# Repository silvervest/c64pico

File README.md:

# C64 Pico

This is a tiny emulated C64 running on a Raspberry Pi Pico! Full details of the build can be found at https://www.youtube.com/watch?v=hgLhGpbC6E4

It was designed to dangle around my neck from a lanyard while I was wandering the halls and sections of PAX Aus 2022. It measures 102x81x16mm!

## Building

Wanna build one yourself? I go over the full build steps of this in the video linked above!

### BOM

I've put together an interactive BOM that you can reference - simply checkout the repo and open `ibom.html` in your browser.

Most of the parts can be figured out from the BOM or schematic, or are generic enough to just pick whatever fits (like all the caps and resistors), but some are pretty specific - here's a few purchasing links from the various sellers I used during this build;

* MicroSD card slot - https://www.aliexpress.com/item/32906952129.html
* TFT LCD - https://www.aliexpress.com/item/32837085500.html
* LCD FPC connector - https://www.digikey.com.au/en/products/detail/cvilux-usa/CF4240FH0R0-05-NH/15793119
* Crappy speaker - https://www.digikey.com.au/en/products/detail/cui-devices/CPT-9019S-SMT-TR/6012432
* Power switch - https://www.digikey.com.au/en/products/detail/c-k/JS102011SAQN/1640095
* Tac switches - https://www.digikey.com.au/en/products/detail/c-k/PTS-647-SN70-SMTR2-LFS/9649854
* LiPo battery - https://www.ebay.com.au/itm/143873020947

### PCBs

I designed the board to be fabricated specifically at JLCPCB with their SMT assembly service, so it should be pretty straightforward to get those made up.

Follow JLCPCB's guide on generating their bom and pos files from Kicad, and the components that can be placed by their SMT assembly service already have the correct and matching LCSC part number associated. Only the back layer needs assembly.

### Programming

The software provided for both the keyboard and MCUME modifications are not what I'd call "production-ready" either, and are really just a hack job. I might clean them up to be merged back one day, but probably not.

The keyboard code is in this repo underneath the keyboard directory, and can be programmed directly onto the ATmega328PB via ICSP headers using the Arduino software.

The RPi Pico code can be found in [my fork of the MCUME repo](https://github.com/silvervest/MCUME/tree/c64pico) under branch `c64pico` and you can follow the main instructions for building, installation and use.

### Face and back plates

The faceplate is just a plain PCB, and the PCB design files can be provided to your fab like any other. I recommend getting it HASL gold covered for extra shiny.

The backplate was designed to be laser cut from 1.5mm-2mm acrylic. I had mine created by [The Laser Cut Shop](https://thelasercutshop.com.au/) and the team there were excellent. I used the plotting function in KiCad to export DXF files for them to use.

## Instructions

Once it's complete, pop your SD card with .PRG files available into the slot and switch it on.

Pick whatever program you'd like to open and press the FIRE joystick button "pew pew". By default, the built-in joystick is "plugged" into JOY1 port, and you can switch that between JOY1/JOY2 using F1/F3 keys. Most C64 games use JOY2, so you might need to experiment.

At the BASIC prompt, type `LOAD` and press RETURN. That will load the .PRG file contents into RAM. Once READY, type `RUN` and press RETURN.

Enjoy! It's a bit slow, and some games are buggy as hell. I love playing Nebulus and Choplifter :)

## Development Photos

An early design, showing the overengineered reimplementation of the RP2040 Pico circuit and power management. It worked, but I didn't like it, so threw most of it out. You can also see I added full diodes into the keyboard for the hell of it.

This was when I was writing the Arduino code for the keyboard and I2C protocol, and a test program running on the Pico decoding it and showing the output.

Finally fully working, so I booted up my favourite C64 game - Nebulus! The screen and battery were still held on with washi tape here.

Also Burnin' Rubber because that game is awesome and runs at almost full speed with no bugs that I could find!

And of course, I've gotta run the classic [10print maze](https://10print.org/)

## Acknowledgements

 - [MCUME](https://github.com/Jean-MarcHarvengt/MCUME)

    The base emulator at the guts of this, and was modified for my purposes.

 - [PICOmputer](https://github.com/bobricius/PICOmputer)

    Heavy inspiration taken from this project (and I stole the UDLR joystick layout)

## License

[CERN OHL v2 Strongly Reciprocal](https://choosealicense.com/licenses/cern-ohl-s-2.0/)

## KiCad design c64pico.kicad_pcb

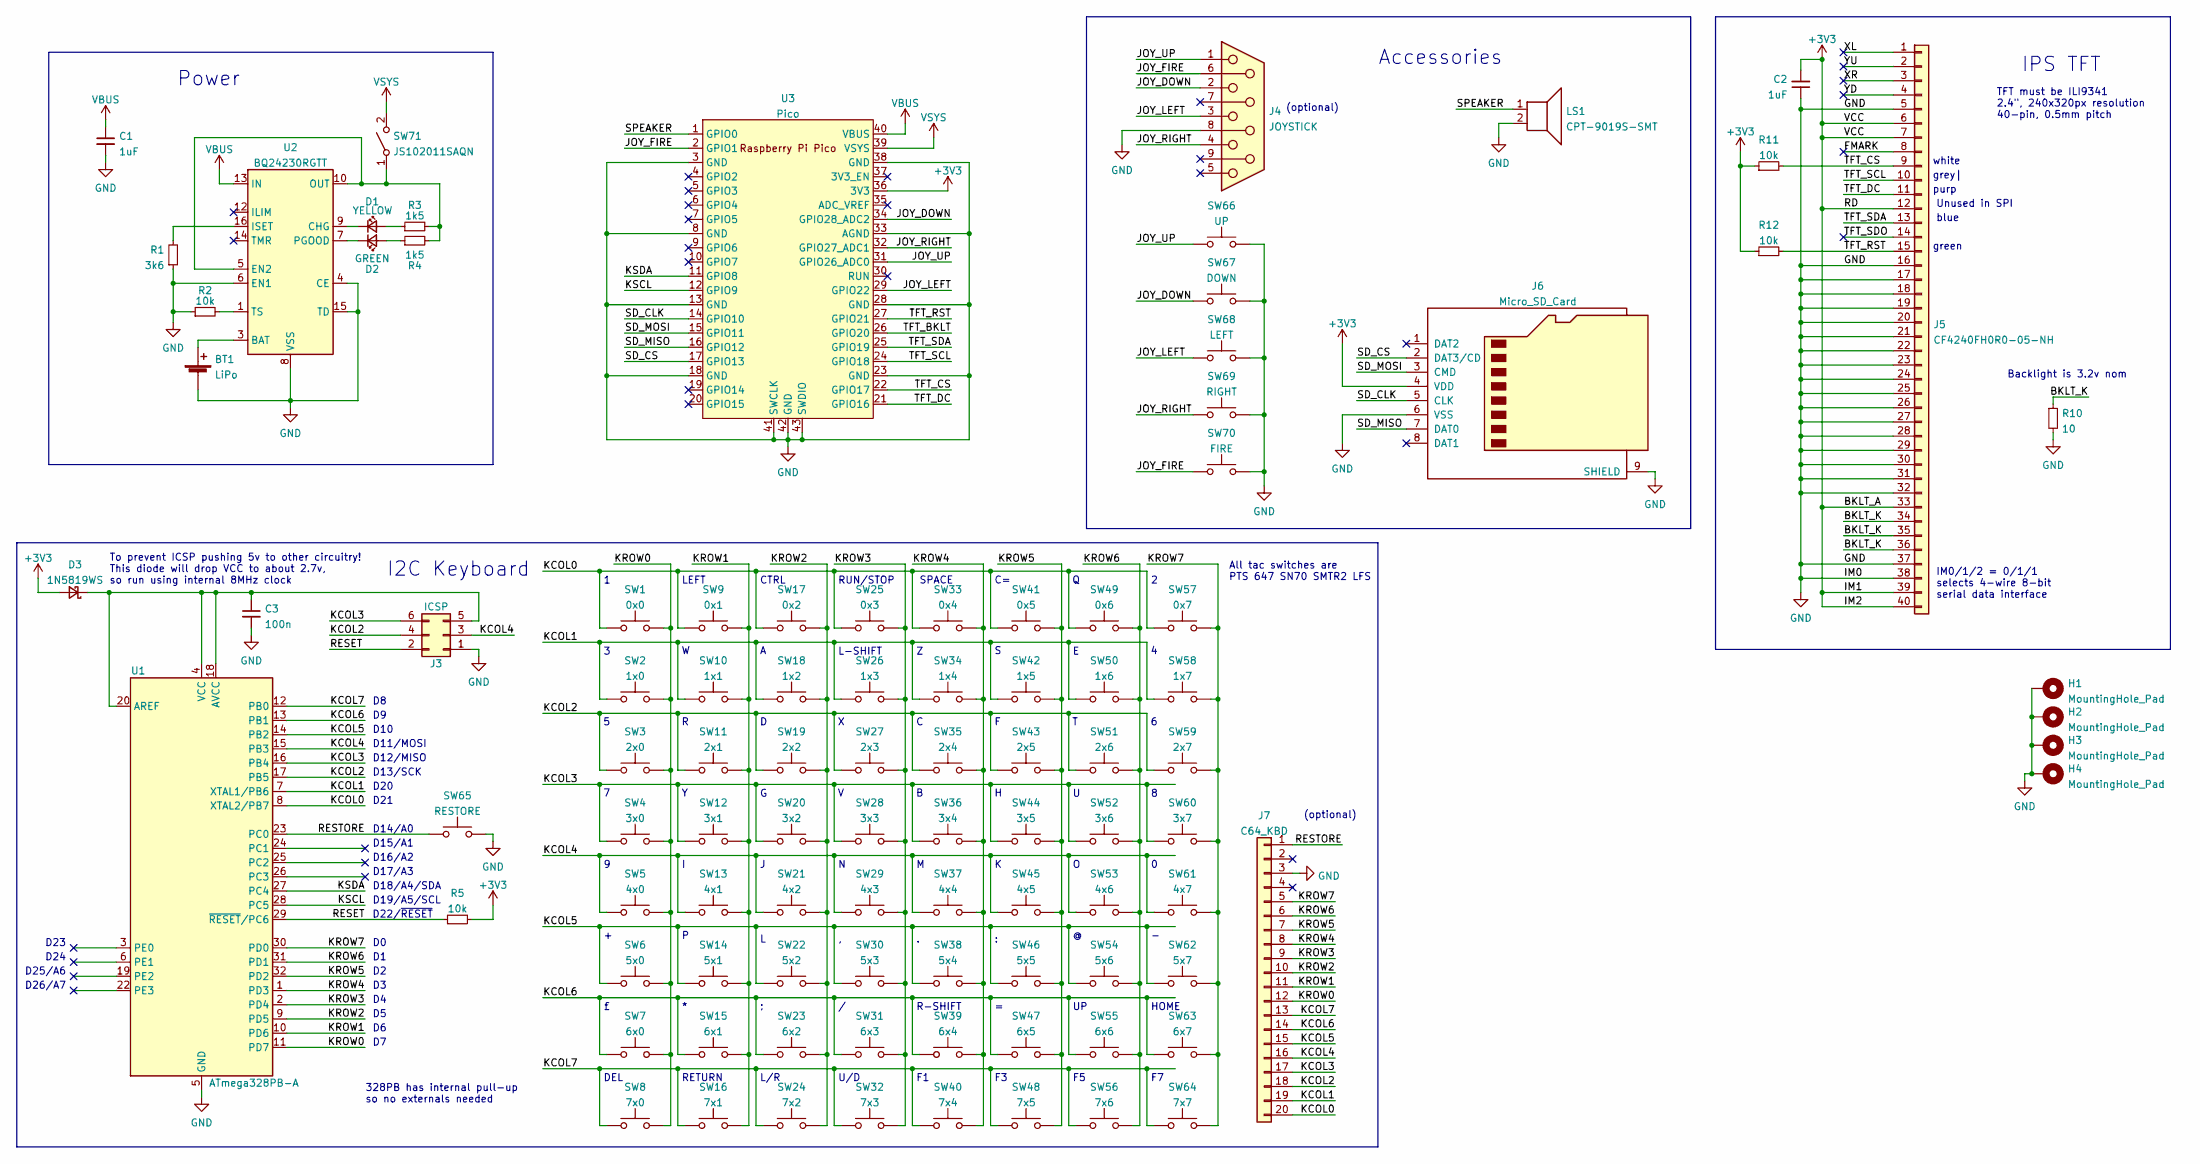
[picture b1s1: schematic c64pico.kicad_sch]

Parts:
BT1: LiPo; JST_PH_S2B-PH-K_1x02_P2.00mm_Horizontal
C1, C2: 1uF; C_0402_1005Metric; LCSC C52923
C3: 100n; C_0402_1005Metric; LCSC C1525
D1: YELLOW; LED_0603_1608Metric; LCSC C72038
D2: GREEN; LED_0603_1608Metric; LCSC C72043
D3: 1N5819WS; D_SOD-323
H1, H2, H3, H4: MountingHole_Pad; MountingHole_2.2mm_M2_Pad
J3: ICSP; PinHeader_2x03_P2.54mm_Vertical
J4: JOYSTICK
J5: CF4240FH0R0-05-NH; ILI9341
J6: Micro_SD_Card; Conn_uSDcard
J7: C64_KBD; PinHeader_1x20_P2.54mm_Vertical
LS1: CPT-9019S-SMT; Buzzer_CUI_CPT-9019S-SMT
R1: 3k6; R_0603_1608Metric; LCSC C22980
R2, R5, R11, R12: 10k; R_0402_1005Metric; LCSC C25744
R3, R4: 1k5; R_0402_1005Metric; LCSC C25867
R10: 10; R_0402_1005Metric
SW1: 0x0; SW_SPST_PTS647
SW2: 1x0; SW_SPST_PTS647
SW3: 2x0; SW_SPST_PTS647
SW4: 3x0; SW_SPST_PTS647
SW5: 4x0; SW_SPST_PTS647
SW6: 5x0; SW_SPST_PTS647
SW7: 6x0; SW_SPST_PTS647
SW8: 7x0; SW_SPST_PTS647
SW9: 0x1; SW_SPST_PTS647
SW10: 1x1; SW_SPST_PTS647
SW11: 2x1; SW_SPST_PTS647
SW12: 3x1; SW_SPST_PTS647
SW13: 4x1; SW_SPST_PTS647
SW14: 5x1; SW_SPST_PTS647
SW15: 6x1; SW_SPST_PTS647
SW16: 7x1; SW_SPST_PTS647
SW17: 0x2; SW_SPST_PTS647
SW18: 1x2; SW_SPST_PTS647
SW19: 2x2; SW_SPST_PTS647
SW20: 3x2; SW_SPST_PTS647
SW21: 4x2; SW_SPST_PTS647
SW22: 5x2; SW_SPST_PTS647
SW23: 6x2; SW_SPST_PTS647
SW24: 7x2; SW_SPST_PTS647
SW25: 0x3; SW_SPST_PTS647
SW26: 1x3; SW_SPST_PTS647
SW27: 2x3; SW_SPST_PTS647
SW28: 3x3; SW_SPST_PTS647
SW29: 4x3; SW_SPST_PTS647
SW30: 5x3; SW_SPST_PTS647
SW31: 6x3; SW_SPST_PTS647
SW32: 7x3; SW_SPST_PTS647
SW33: 0x4; SW_SPST_PTS647
SW34: 1x4; SW_SPST_PTS647
SW35: 2x4; SW_SPST_PTS647
SW36: 3x4; SW_SPST_PTS647
SW37: 4x4; SW_SPST_PTS647
SW38: 5x4; SW_SPST_PTS647
SW39: 6x4; SW_SPST_PTS647
SW40: 7x4; SW_SPST_PTS647
SW41: 0x5; SW_SPST_PTS647
SW42: 1x5; SW_SPST_PTS647
SW43: 2x5; SW_SPST_PTS647
SW44: 3x5; SW_SPST_PTS647
SW45: 4x5; SW_SPST_PTS647
SW46: 5x5; SW_SPST_PTS647
SW47: 6x5; SW_SPST_PTS647
SW48: 7x5; SW_SPST_PTS647
SW49: 0x6; SW_SPST_PTS647
SW50: 1x6; SW_SPST_PTS647
SW51: 2x6; SW_SPST_PTS647
SW52: 3x6; SW_SPST_PTS647
SW53: 4x6; SW_SPST_PTS647
SW54: 5x6; SW_SPST_PTS647
SW55: 6x6; SW_SPST_PTS647
SW56: 7x6; SW_SPST_PTS647
SW57: 0x7; SW_SPST_PTS647
SW58: 1x7; SW_SPST_PTS647
SW59: 2x7; SW_SPST_PTS647
SW60: 3x7; SW_SPST_PTS647
SW61: 4x7; SW_SPST_PTS647
SW62: 5x7; SW_SPST_PTS647
SW63: 6x7; SW_SPST_PTS647
SW64: 7x7; SW_SPST_PTS647
SW65: RESTORE; SW_SPST_PTS647
SW66: UP; SW_SPST_PTS647
SW67: DOWN; SW_SPST_PTS647
SW68: LEFT; SW_SPST_PTS647
SW69: RIGHT; SW_SPST_PTS647
SW70: FIRE; SW_SPST_PTS647
SW71: JS102011SAQN; SW_SPDT_CK-JS102011SAQN
U1: ATmega328PB-A; TQFP-32_7x7mm_P0.8mm
U2: BQ24230RGTT; VQFN-16-1EP_3x3mm_P0.5mm_EP1.68x1.68mm_ThermalVias; LCSC C138361
U3: Pico; RPi_Pico_SMD

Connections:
+3V3: C2.2, D3.2 (A), J5.6, J5.7, J5.12, J5.33, J5.39, J5.40, J6.4 (VDD), R5.2, R11.1, R12.1, U3.36 (3V3)
/BKLT_K: J5.34, J5.35, J5.36, R10.1
/FMARK: J5.8
/JOY_DOWN: J4.2, SW67.1, U3.34 (GPIO28_ADC2)
/JOY_FIRE: J4.6, SW70.1, U3.2 (GPIO1)
/JOY_LEFT: J4.3, SW68.1, U3.29 (GPIO22)
/JOY_RIGHT: J4.4, SW69.1, U3.32 (GPIO27_ADC1)
/JOY_UP: J4.1, SW66.1, U3.31 (GPIO26_ADC0)
/KCOL0: J7.20, SW1.1, SW9.1, SW17.1, SW25.1, SW33.1, SW41.1, SW49.1, SW57.1, U1.8 (XTAL2/PB7)
/KCOL1: J7.19, SW2.1, SW10.1, SW18.1, SW26.1, SW34.1, SW42.1, SW50.1, SW58.1, U1.7 (XTAL1/PB6)
/KCOL2: J3.4, J7.18, SW3.1, SW11.1, SW19.1, SW27.1, SW35.1, SW43.1, SW51.1, SW59.1, U1.17 (PB5)
/KCOL3: J3.6, J7.17, SW4.1, SW12.1, SW20.1, SW28.1, SW36.1, SW44.1, SW52.1, SW60.1, U1.16 (PB4)
/KCOL4: J3.3, J7.16, SW5.1, SW13.1, SW21.1, SW29.1, SW37.1, SW45.1, SW53.1, SW61.1, U1.15 (PB3)
/KCOL5: J7.15, SW6.1, SW14.1, SW22.1, SW30.1, SW38.1, SW46.1, SW54.1, SW62.1, U1.14 (PB2)
/KCOL6: J7.14, SW7.1, SW15.1, SW23.1, SW31.1, SW39.1, SW47.1, SW55.1, SW63.1, U1.13 (PB1)
/KCOL7: J7.13, SW8.1, SW16.1, SW24.1, SW32.1, SW40.1, SW48.1, SW56.1, SW64.1, U1.12 (PB0)
/KROW0: J7.12, SW1.2, SW2.2, SW3.2, SW4.2, SW5.2, SW6.2, SW7.2, SW8.2, U1.11 (PD7)
/KROW1: J7.11, SW9.2, SW10.2, SW11.2, SW12.2, SW13.2, SW14.2, SW15.2, SW16.2, U1.10 (PD6)
/KROW2: J7.10, SW17.2, SW18.2, SW19.2, SW20.2, SW21.2, SW22.2, SW23.2, SW24.2, U1.9 (PD5)
/KROW3: J7.9, SW25.2, SW26.2, SW27.2, SW28.2, SW29.2, SW30.2, SW31.2, SW32.2, U1.2 (PD4)
/KROW4: J7.8, SW33.2, SW34.2, SW35.2, SW36.2, SW37.2, SW38.2, SW39.2, SW40.2, U1.1 (PD3)
/KROW5: J7.7, SW41.2, SW42.2, SW43.2, SW44.2, SW45.2, SW46.2, SW47.2, SW48.2, U1.32 (PD2)
/KROW6: J7.6, SW49.2, SW50.2, SW51.2, SW52.2, SW53.2, SW54.2, SW55.2, SW56.2, U1.31 (PD1)
/KROW7: J7.5, SW57.2, SW58.2, SW59.2, SW60.2, SW61.2, SW62.2, SW63.2, SW64.2, U1.30 (PD0)
/KSCL: U1.28 (PC5), U3.12 (GPIO9)
/KSDA: U1.27 (PC4), U3.11 (GPIO8)
/RESET: J3.2, R5.1, U1.29 (~RESET/PC6)
/RESTORE: J7.1, SW65.1, U1.23 (PC0)
/SD_CLK: J6.5 (CLK), U3.14 (GPIO10)
/SD_CS: J6.2 (DAT3/CD), U3.17 (GPIO13)
/SD_MISO: J6.7 (DAT0), U3.16 (GPIO12)
/SD_MOSI: J6.3 (CMD), U3.15 (GPIO11)
/SPEAKER: LS1.1, U3.1 (GPIO0)
/TFT_BKLT: U3.26 (GPIO20)
/TFT_CS: J5.9, R11.2, U3.22 (GPIO17)
/TFT_DC: J5.11, U3.21 (GPIO16)
/TFT_RST: J5.15, R12.2, U3.27 (GPIO21)
/TFT_SCL: J5.10, U3.24 (GPIO18)
/TFT_SDA: J5.13, U3.25 (GPIO19)
/TFT_SDO: J5.14
/XL: J5.1
/XR: J5.3
/YD: J5.4
/YU: J5.2
GND: BT1.2 (-), C1.2, C2.1, C3.2, H1.1, H2.1, H3.1, H4.1, J3.1, J4.8, J5.5, J5.16, J5.17, J5.18, J5.19, J5.20, J5.21, J5.22, J5.23, J5.24, J5.25, J5.26, J5.27, J5.28, J5.29, J5.30, J5.31, J5.32, J5.37, J5.38, J6.6 (VSS), J6.9 (SHIELD), J7.3, LS1.2, R1.1, R2.1, R10.2, SW65.2, SW66.2, SW67.2, SW68.2, SW69.2, SW70.2, U1.5 (GND), U1.21 (GND), U2.4 (CE), U2.6 (EN1), U2.8 (VSS), U2.15 (TD), U2.17 (VSS), U3.3 (GND), U3.8 (GND), U3.13 (GND), U3.18 (GND), U3.23 (GND), U3.28 (GND), U3.33 (AGND), U3.38 (GND), U3.41 (SWCLK), U3.42 (GND), U3.43 (SWDIO)
unnamed: BT1.1 (+), U2.2 (BAT), U2.3 (BAT)
unnamed: C3.1, D3.1 (K), J3.5, U1.4 (VCC), U1.18 (AVCC), U1.20 (AREF)
unnamed: D1.1 (K), U2.9 (CHG)
unnamed: D1.2 (A), R3.1
unnamed: D2.1 (K), U2.7 (PGOOD)
unnamed: D2.2 (A), R4.1
unnamed: R1.2, U2.16 (ISET)
unnamed: R2.2, U2.1 (TS)
unnamed: R3.2, R4.2, SW71.1 (A), U2.5 (EN2), U2.10 (OUT), U2.11 (OUT)
VBUS: C1.1, U2.13 (IN), U3.40 (VBUS)
VSYS: SW71.2 (B), U3.39 (VSYS)

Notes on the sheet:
D22/~{RESET}
LEFT
All tac switches are PTS 647 SN70 SMTR2 LFS
D20
328PB has internal pull-up so no externals needed
TFT must be ILI9341 2.4", 240x320px resolution 40-pin, 0.5mm pitch
To prevent ICSP pushing 5v to other circuitry! This diode will drop VCC to about 2.7v, so run using internal 8MHz clock
RUN/STOP
RETURN
U/D
purp
D19/A5/SCL
R-SHIFT
Accessories
D21
Backlight is 3.2v nom
D11/MOSI
SPACE
CTRL
IM0/1/2 = 0/1/1 selects 4-wire 8-bit serial data interface
L/R
grey|
D25/A6
(optional)
D14/A0
white
HOME
I2C Keyboard
D23
Power
blue
D10
D13/SCK
D12/MISO
D18/A4/SDA
L-SHIFT
D26/A7
DEL
IPS TFT
D24

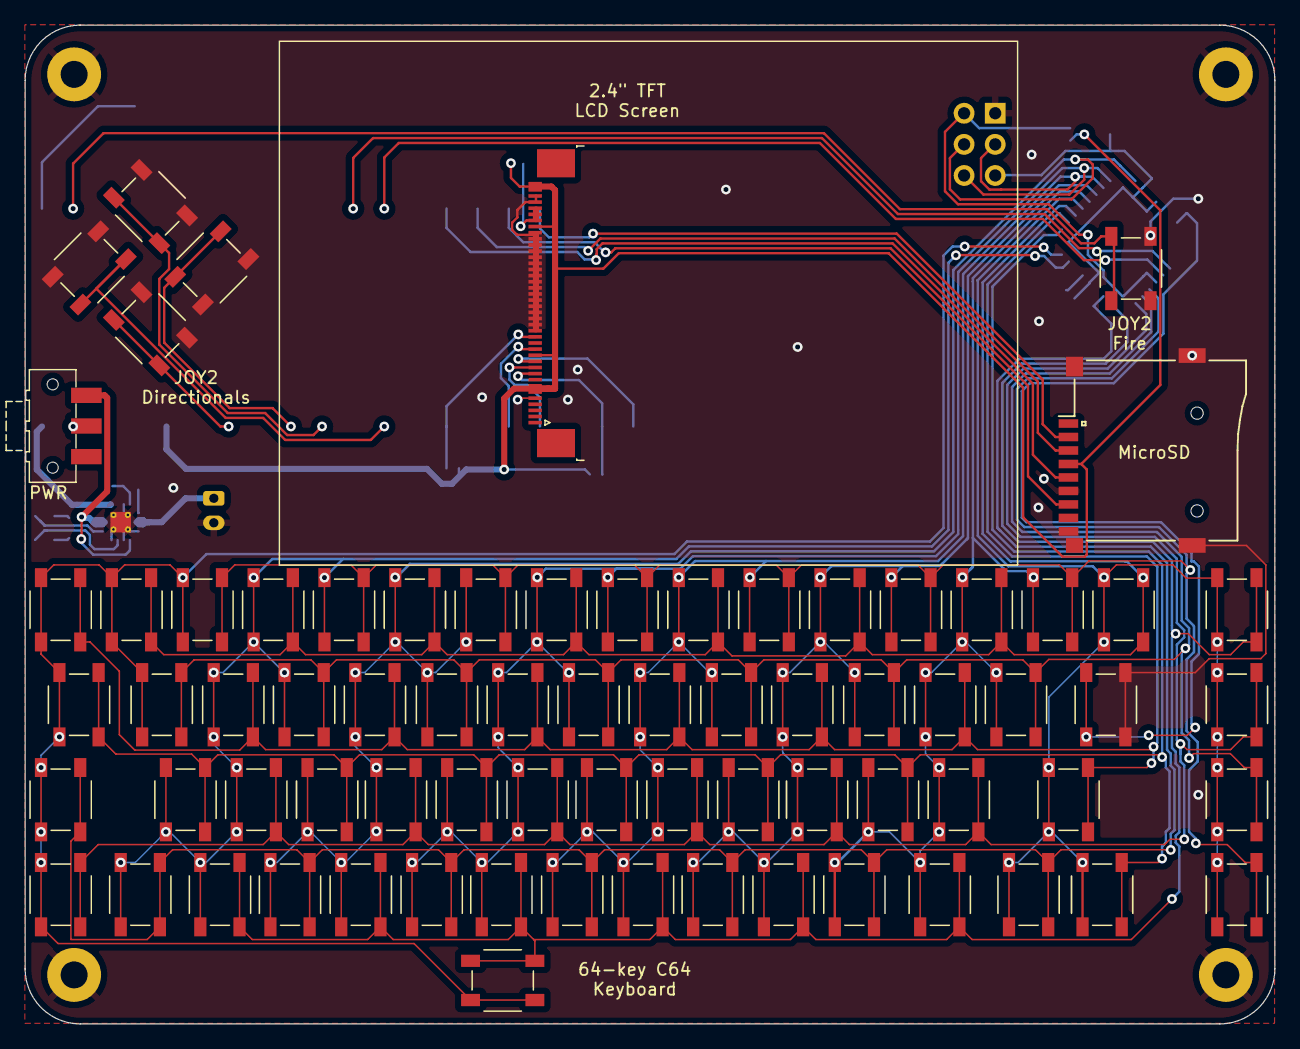
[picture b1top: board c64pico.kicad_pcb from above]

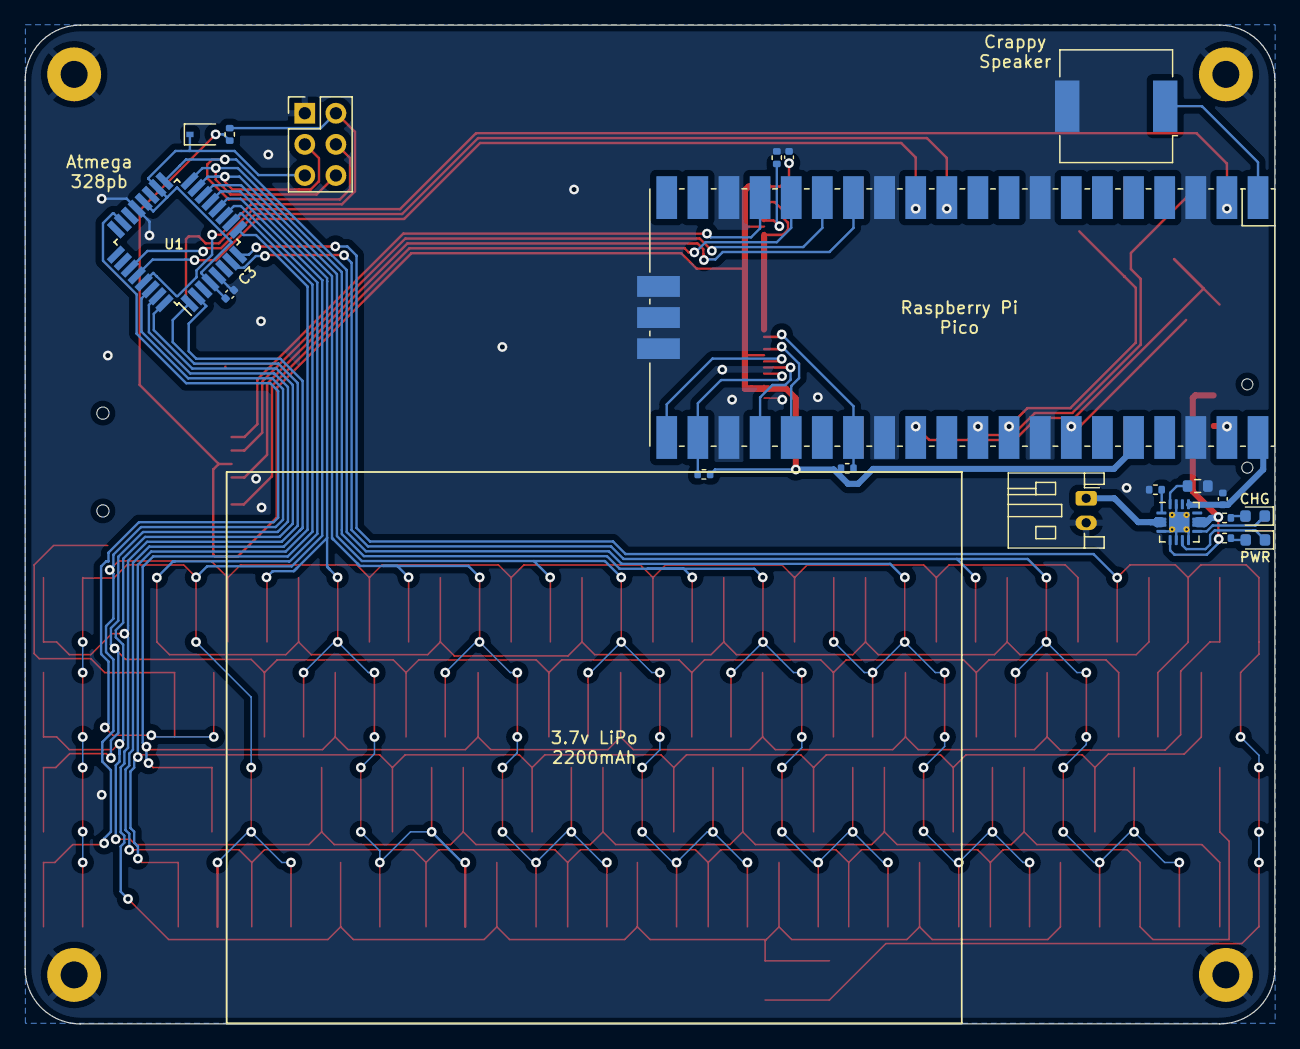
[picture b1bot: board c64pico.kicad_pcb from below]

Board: 2 copper layers, 102.0 x 81.5 mm, 97 parts (20 on the bottom side), 49 nets.

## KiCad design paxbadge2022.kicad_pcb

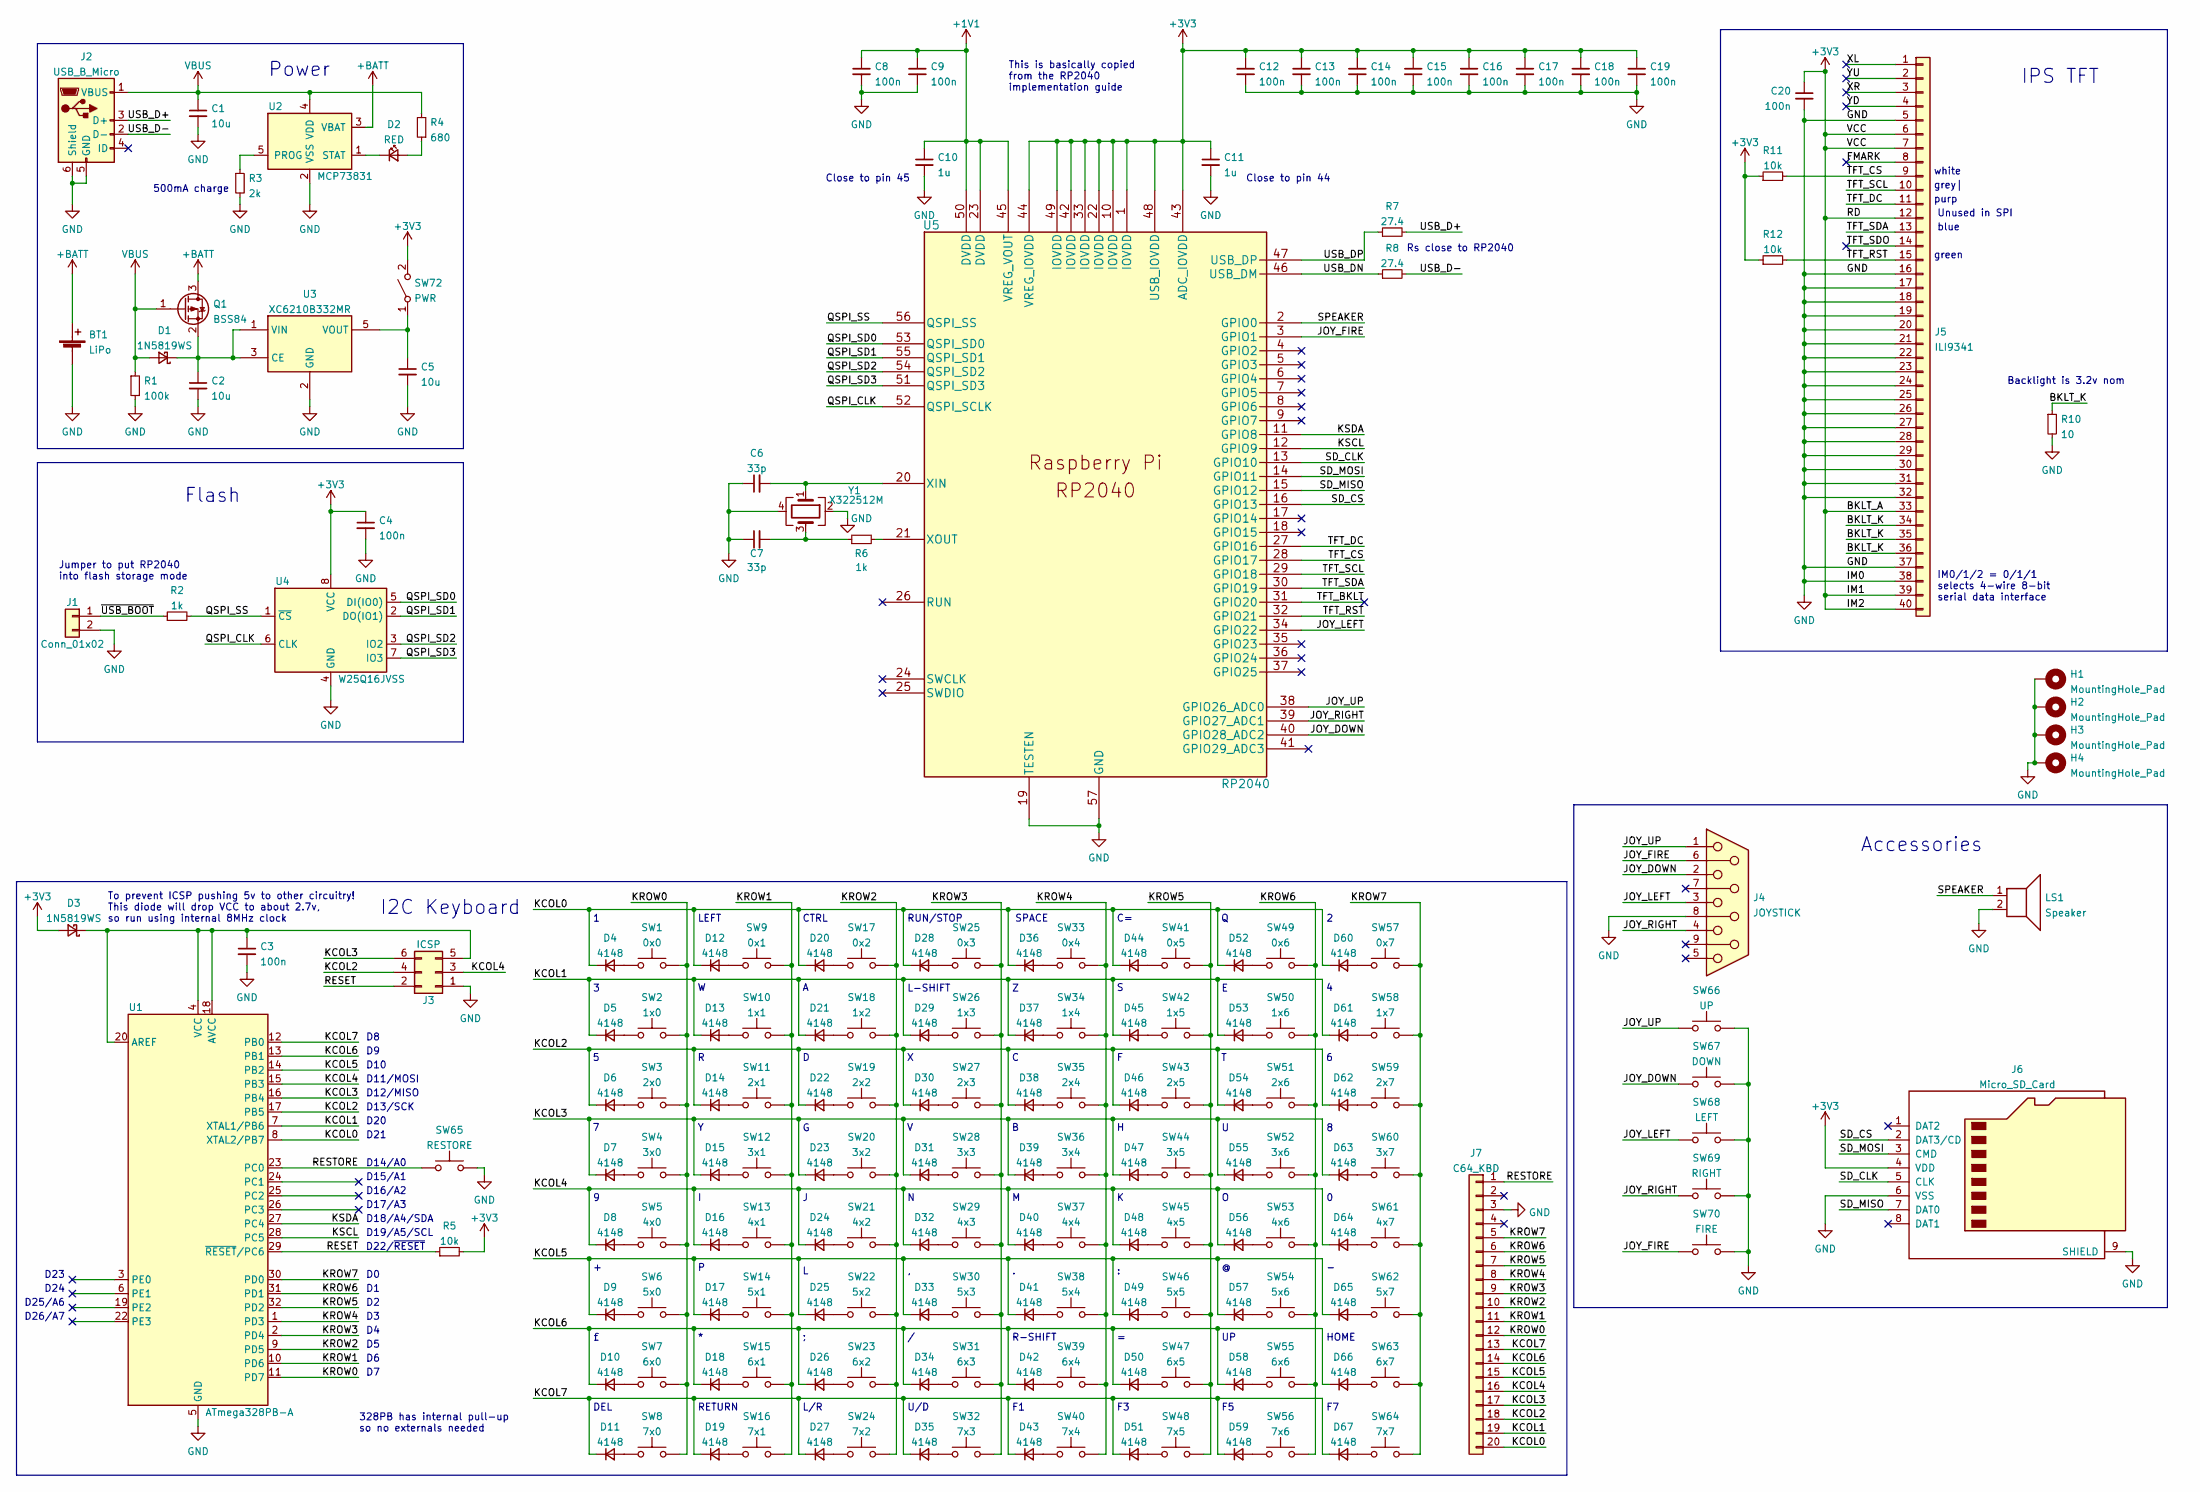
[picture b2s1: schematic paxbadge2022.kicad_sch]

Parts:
BT1: LiPo; JST_PH_S2B-PH-K_1x02_P2.00mm_Horizontal
C1, C2, C5: 10u; C_0603_1608Metric; LCSC C19702
C3, C4: 100n; C_0402_1005Metric; LCSC C1525
C6: 33p; C_0402_1005Metric; LCSC C1562
C7: 33p; C_0402_1005Metric
C8, C9, C12, C13, C14, C15, C16, C17, C18, C19, C20: 100n; C_0402_1005Metric
C10: 1u; C_0402_1005Metric; LCSC C52923
C11: 1u; C_0402_1005Metric
D1: 1N5819WS; D_SOD-323; LCSC C191023
D2: RED; LED_D3.0mm; LCSC C2286
D3: 1N5819WS; D_SOD-323
D4, D5, D6, D7, D8, D9, D10, D11, D12, D13, D14, D15, D16, D17, D18, D19, D20, D21, D22, D23, D24, D25, D26, D27, D28, D29, D30, D31, D32, D33, D34, D35, D36, D37, D38, D39, D40, D41, D42, D43, D44, D45, D46, D47, D48, D49, D50, D51, D52, D53, D54, D55, D56, D57, D58, D59, D60, D61, D62, D63, D64, D65, D66, D67: 4148; D_SOD-323F
H1, H2, H3, H4: MountingHole_Pad; MountingHole_2.2mm_M2_Pad
J1: Conn_01x02; PinHeader_1x02_P2.54mm_Vertical
J2: USB_B_Micro; USB_Micro-B_Amphenol_10118194_Horizontal
J3: ICSP; PinHeader_2x03_P2.54mm_Vertical
J4: JOYSTICK
J5: ILI9341
J6: Micro_SD_Card; Conn_uSDcard
J7: C64_KBD; PinHeader_1x20_P2.54mm_Vertical
LS1: Speaker; Buzzer_CUI_CPT-9019S-SMT
Q1: BSS84; SOT-23; LCSC C8492
R1: 100k; R_0402_1005Metric; LCSC C25741
R2: 1k; R_0402_1005Metric; LCSC C11702
R3: 2k; R_0402_1005Metric; LCSC C4109
R4: 680; R_0402_1005Metric; LCSC C25130
R5, R11, R12: 10k; R_0402_1005Metric; LCSC C25744
R6: 1k; R_0402_1005Metric
R7: 27.4; R_0402_1005Metric; LCSC C25100
R8: 27.4; R_0402_1005Metric
R10: 10; R_0402_1005Metric
SW1: 0x0; SW_SPST_PTS647
SW2: 1x0; SW_SPST_PTS647
SW3: 2x0; SW_SPST_PTS647
SW4: 3x0; SW_SPST_PTS647
SW5: 4x0; SW_SPST_PTS647
SW6: 5x0; SW_SPST_PTS647
SW7: 6x0; SW_SPST_PTS647
SW8: 7x0; SW_SPST_PTS647
SW9: 0x1; SW_SPST_PTS647
SW10: 1x1; SW_SPST_PTS647
SW11: 2x1; SW_SPST_PTS647
SW12: 3x1; SW_SPST_PTS647
SW13: 4x1; SW_SPST_PTS647
SW14: 5x1; SW_SPST_PTS647
SW15: 6x1; SW_SPST_PTS647
SW16: 7x1; SW_SPST_PTS647
SW17: 0x2; SW_SPST_PTS647
SW18: 1x2; SW_SPST_PTS647
SW19: 2x2; SW_SPST_PTS647
SW20: 3x2; SW_SPST_PTS647
SW21: 4x2; SW_SPST_PTS647
SW22: 5x2; SW_SPST_PTS647
SW23: 6x2; SW_SPST_PTS647
SW24: 7x2; SW_SPST_PTS647
SW25: 0x3; SW_SPST_PTS647
SW26: 1x3; SW_SPST_PTS647
SW27: 2x3; SW_SPST_PTS647
SW28: 3x3; SW_SPST_PTS647
SW29: 4x3; SW_SPST_PTS647
SW30: 5x3; SW_SPST_PTS647
SW31: 6x3; SW_SPST_PTS647
SW32: 7x3; SW_SPST_PTS647
SW33: 0x4; SW_SPST_PTS647
SW34: 1x4; SW_SPST_PTS647
SW35: 2x4; SW_SPST_PTS647
SW36: 3x4; SW_SPST_PTS647
SW37: 4x4; SW_SPST_PTS647
SW38: 5x4; SW_SPST_PTS647
SW39: 6x4; SW_SPST_PTS647
SW40: 7x4; SW_SPST_PTS647
SW41: 0x5; SW_SPST_PTS647
SW42: 1x5; SW_SPST_PTS647
SW43: 2x5; SW_SPST_PTS647
SW44: 3x5; SW_SPST_PTS647
SW45: 4x5; SW_SPST_PTS647
SW46: 5x5; SW_SPST_PTS647
SW47: 6x5; SW_SPST_PTS647
SW48: 7x5; SW_SPST_PTS647
SW49: 0x6; SW_SPST_PTS647
SW50: 1x6; SW_SPST_PTS647
SW51: 2x6; SW_SPST_PTS647
SW52: 3x6; SW_SPST_PTS647
SW53: 4x6; SW_SPST_PTS647
SW54: 5x6; SW_SPST_PTS647
SW55: 6x6; SW_SPST_PTS647
SW56: 7x6; SW_SPST_PTS647
SW57: 0x7; SW_SPST_PTS647
SW58: 1x7; SW_SPST_PTS647
SW59: 2x7; SW_SPST_PTS647
SW60: 3x7; SW_SPST_PTS647
SW61: 4x7; SW_SPST_PTS647
SW62: 5x7; SW_SPST_PTS647
SW63: 6x7; SW_SPST_PTS647
SW64: 7x7; SW_SPST_PTS647
SW65: RESTORE; SW_SPST_PTS647
SW66: UP; SW_SPST_PTS647
SW67: DOWN; SW_SPST_PTS647
SW68: LEFT; SW_SPST_PTS647
SW69: RIGHT; SW_SPST_PTS647
SW70: FIRE; SW_SPST_PTS647
SW72: PWR; SW_SPDT_CK-JS102011SAQN
U1: ATmega328PB-A; TQFP-32_7x7mm_P0.8mm
U2: MCP73831; SOT-23-5; LCSC C14879
U3: XC6210B332MR; SOT-23-5; LCSC C47719
U4: W25Q16JVSS; SOIC-8_5.23x5.23mm_P1.27mm; LCSC C82317
U5: RP2040; LCSC C2040
Y1: X322512M; Crystal_SMD_3225-4Pin_3.2x2.5mm; LCSC C9002

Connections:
+1V1: C8.1, C9.1, C10.1, U5.23 (DVDD), U5.45 (VREG_VOUT), U5.50 (DVDD)
+3V3: C4.1, C11.1, C12.1, C13.1, C14.1, C15.1, C16.1, C17.1, C18.1, C19.1, C20.1, D3.2 (A), J5.6, J5.7, J5.12, J5.33, J5.39, J5.40, J6.4 (VDD), R5.2, R11.1, R12.1, SW72.2 (B), U4.8 (VCC), U5.1 (IOVDD), U5.10 (IOVDD), U5.22 (IOVDD), U5.33 (IOVDD), U5.42 (IOVDD), U5.43 (ADC_IOVDD), U5.44 (VREG_IOVDD), U5.48 (USB_IOVDD), U5.49 (IOVDD)
+BATT: BT1.1 (+), Q1.3 (D), U2.3 (VBAT)
/BKLT_K: J5.34, J5.35, J5.36, R10.1
/FMARK: J5.8
/JOY_DOWN: J4.2, SW67.1, U5.40 (GPIO28_ADC2)
/JOY_FIRE: J4.6, SW70.1, U5.3 (GPIO1)
/JOY_LEFT: J4.3, SW68.1, U5.34 (GPIO22)
/JOY_RIGHT: J4.4, SW69.1, U5.39 (GPIO27_ADC1)
/JOY_UP: J4.1, SW66.1, U5.38 (GPIO26_ADC0)
/KCOL0: D4.1 (K), D12.1 (K), D20.1 (K), D28.1 (K), D36.1 (K), D44.1 (K), D52.1 (K), D60.1 (K), J7.20, U1.8 (XTAL2/PB7)
/KCOL1: D5.1 (K), D13.1 (K), D21.1 (K), D29.1 (K), D37.1 (K), D45.1 (K), D53.1 (K), D61.1 (K), J7.19, U1.7 (XTAL1/PB6)
/KCOL2: D6.1 (K), D14.1 (K), D22.1 (K), D30.1 (K), D38.1 (K), D46.1 (K), D54.1 (K), D62.1 (K), J3.4, J7.18, U1.17 (PB5)
/KCOL3: D7.1 (K), D15.1 (K), D23.1 (K), D31.1 (K), D39.1 (K), D47.1 (K), D55.1 (K), D63.1 (K), J3.6, J7.17, U1.16 (PB4)
/KCOL4: D8.1 (K), D16.1 (K), D24.1 (K), D32.1 (K), D40.1 (K), D48.1 (K), D56.1 (K), D64.1 (K), J3.3, J7.16, U1.15 (PB3)
/KCOL5: D9.1 (K), D17.1 (K), D25.1 (K), D33.1 (K), D41.1 (K), D49.1 (K), D57.1 (K), D65.1 (K), J7.15, U1.14 (PB2)
/KCOL6: D10.1 (K), D18.1 (K), D26.1 (K), D34.1 (K), D42.1 (K), D50.1 (K), D58.1 (K), D66.1 (K), J7.14, U1.13 (PB1)
/KCOL7: D11.1 (K), D19.1 (K), D27.1 (K), D35.1 (K), D43.1 (K), D51.1 (K), D59.1 (K), D67.1 (K), J7.13, U1.12 (PB0)
/KROW0: J7.12, SW1.2, SW2.2, SW3.2, SW4.2, SW5.2, SW6.2, SW7.2, SW8.2, U1.11 (PD7)
/KROW1: J7.11, SW9.2, SW10.2, SW11.2, SW12.2, SW13.2, SW14.2, SW15.2, SW16.2, U1.10 (PD6)
/KROW2: J7.10, SW17.2, SW18.2, SW19.2, SW20.2, SW21.2, SW22.2, SW23.2, SW24.2, U1.9 (PD5)
/KROW3: J7.9, SW25.2, SW26.2, SW27.2, SW28.2, SW29.2, SW30.2, SW31.2, SW32.2, U1.2 (PD4)
/KROW4: J7.8, SW33.2, SW34.2, SW35.2, SW36.2, SW37.2, SW38.2, SW39.2, SW40.2, U1.1 (PD3)
/KROW5: J7.7, SW41.2, SW42.2, SW43.2, SW44.2, SW45.2, SW46.2, SW47.2, SW48.2, U1.32 (PD2)
/KROW6: J7.6, SW49.2, SW50.2, SW51.2, SW52.2, SW53.2, SW54.2, SW55.2, SW56.2, U1.31 (PD1)
/KROW7: J7.5, SW57.2, SW58.2, SW59.2, SW60.2, SW61.2, SW62.2, SW63.2, SW64.2, U1.30 (PD0)
/KSCL: U1.28 (PC5), U5.12 (GPIO9)
/KSDA: U1.27 (PC4), U5.11 (GPIO8)
/QSPI_CLK: U4.6 (CLK), U5.52 (QSPI_SCLK)
/QSPI_SD0: U4.5 (DI(IO0)), U5.53 (QSPI_SD0)
/QSPI_SD1: U4.2 (DO(IO1)), U5.55 (QSPI_SD1)
/QSPI_SD2: U4.3 (IO2), U5.54 (QSPI_SD2)
/QSPI_SD3: U4.7 (IO3), U5.51 (QSPI_SD3)
/QSPI_SS: R2.2, U4.1 (~CS), U5.56 (QSPI_SS)
/RESET: J3.2, R5.1, U1.29 (~RESET/PC6)
/RESTORE: J7.1, SW65.1, U1.23 (PC0)
/SD_CLK: J6.5 (CLK), U5.13 (GPIO10)
/SD_CS: J6.2 (DAT3/CD), U5.16 (GPIO13)
/SD_MISO: J6.7 (DAT0), U5.15 (GPIO12)
/SD_MOSI: J6.3 (CMD), U5.14 (GPIO11)
/SPEAKER: LS1.1, U5.2 (GPIO0)
/TFT_BKLT: U5.31 (GPIO20)
/TFT_CS: J5.9, R11.2, U5.28 (GPIO17)
/TFT_DC: J5.11, U5.27 (GPIO16)
/TFT_RST: J5.15, R12.2, U5.32 (GPIO21)
/TFT_SCL: J5.10, U5.29 (GPIO18)
/TFT_SDA: J5.13, U5.30 (GPIO19)
/TFT_SDO: J5.14
/USB_D+: J2.3 (D+), R7.2
/USB_D-: J2.2 (D-), R8.2
/USB_DN: R8.1, U5.46 (USB_DM)
/USB_DP: R7.1, U5.47 (USB_DP)
/XL: J5.1
/XR: J5.3
/YD: J5.4
/YU: J5.2
/~USB_BOOT: J1.1, R2.1
GND: BT1.2 (-), C1.2, C2.2, C3.2, C4.2, C5.2, C6.1, C7.1, C8.2, C9.2, C10.2, C11.2, C12.2, C13.2, C14.2, C15.2, C16.2, C17.2, C18.2, C19.2, C20.2, H1.1, H2.1, H3.1, H4.1, J1.2, J2.5 (GND), J2.6 (Shield), J3.1, J4.8, J5.5, J5.16, J5.17, J5.18, J5.19, J5.20, J5.21, J5.22, J5.23, J5.24, J5.25, J5.26, J5.27, J5.28, J5.29, J5.30, J5.31, J5.32, J5.37, J5.38, J6.6 (VSS), J6.9 (SHIELD), J7.3, LS1.2, R1.2, R3.2, R10.2, SW65.2, SW66.2, SW67.2, SW68.2, SW69.2, SW70.2, U1.5 (GND), U1.21 (GND), U2.2 (VSS), U3.2 (GND), U4.4 (GND), U5.19 (TESTEN), U5.57 (GND), Y1.2, Y1.4
unnamed: C2.1, D1.1 (K), Q1.2 (S), U3.1 (VIN), U3.3 (CE)
unnamed: C3.1, D3.1 (K), J3.5, U1.4 (VCC), U1.18 (AVCC), U1.20 (AREF)
unnamed: C5.1, SW72.1 (A), U3.5 (VOUT)
unnamed: C6.2, U5.20 (XIN), Y1.1
unnamed: C7.2, R6.1, Y1.3
unnamed: D2.1 (K), U2.1 (STAT)
unnamed: D2.2 (A), R4.1
unnamed: D4.2 (A), SW1.1
unnamed: D5.2 (A), SW2.1
unnamed: D6.2 (A), SW3.1
unnamed: D7.2 (A), SW4.1
unnamed: D8.2 (A), SW5.1
unnamed: D9.2 (A), SW6.1
unnamed: D10.2 (A), SW7.1
unnamed: D11.2 (A), SW8.1
unnamed: D12.2 (A), SW9.1
unnamed: D13.2 (A), SW10.1
unnamed: D14.2 (A), SW11.1
unnamed: D15.2 (A), SW12.1
unnamed: D16.2 (A), SW13.1
unnamed: D17.2 (A), SW14.1
unnamed: D18.2 (A), SW15.1
unnamed: D19.2 (A), SW16.1
unnamed: D20.2 (A), SW17.1
unnamed: D21.2 (A), SW18.1
unnamed: D22.2 (A), SW19.1
unnamed: D23.2 (A), SW20.1
unnamed: D24.2 (A), SW21.1
unnamed: D25.2 (A), SW22.1
unnamed: D26.2 (A), SW23.1
unnamed: D27.2 (A), SW24.1
unnamed: D28.2 (A), SW25.1
unnamed: D29.2 (A), SW26.1
unnamed: D30.2 (A), SW27.1
unnamed: D31.2 (A), SW28.1
unnamed: D32.2 (A), SW29.1
unnamed: D33.2 (A), SW30.1
unnamed: D34.2 (A), SW31.1
unnamed: D35.2 (A), SW32.1
unnamed: D36.2 (A), SW33.1
unnamed: D37.2 (A), SW34.1
unnamed: D38.2 (A), SW35.1
unnamed: D39.2 (A), SW36.1
unnamed: D40.2 (A), SW37.1
unnamed: D41.2 (A), SW38.1
unnamed: D42.2 (A), SW39.1
unnamed: D43.2 (A), SW40.1
unnamed: D44.2 (A), SW41.1
unnamed: D45.2 (A), SW42.1
unnamed: D46.2 (A), SW43.1
unnamed: D47.2 (A), SW44.1
unnamed: D48.2 (A), SW45.1
unnamed: D49.2 (A), SW46.1
unnamed: D50.2 (A), SW47.1
unnamed: D51.2 (A), SW48.1
unnamed: D52.2 (A), SW49.1
unnamed: D53.2 (A), SW50.1
unnamed: D54.2 (A), SW51.1
unnamed: D55.2 (A), SW52.1
unnamed: D56.2 (A), SW53.1
unnamed: D57.2 (A), SW54.1
unnamed: D58.2 (A), SW55.1
unnamed: D59.2 (A), SW56.1
unnamed: D60.2 (A), SW57.1
unnamed: D61.2 (A), SW58.1
unnamed: D62.2 (A), SW59.1
unnamed: D63.2 (A), SW60.1
unnamed: D64.2 (A), SW61.1
unnamed: D65.2 (A), SW62.1
unnamed: D66.2 (A), SW63.1
unnamed: D67.2 (A), SW64.1
unnamed: R3.1, U2.5 (PROG)
unnamed: R6.2, U5.21 (XOUT)
VBUS: C1.1, D1.2 (A), J2.1 (VBUS), Q1.1 (G), R1.1, R4.2, U2.4 (VDD)

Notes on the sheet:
D22/~{RESET}
LEFT
D20
328PB has internal pull-up so no externals needed
To prevent ICSP pushing 5v to other circuitry! This diode will drop VCC to about 2.7v, so run using internal 8MHz clock
RUN/STOP
Flash
RETURN
U/D
purp
D19/A5/SCL
R-SHIFT
Accessories
D21
Backlight is 3.2v nom
D11/MOSI
SPACE
CTRL
IM0/1/2 = 0/1/1 selects 4-wire 8-bit serial data interface
L/R
grey|
Rs close to RP2040
D25/A6
Jumper to put RP2040 into flash storage mode
D14/A0
white
HOME
I2C Keyboard
D23
Power
Close to pin 45
blue
D10
D13/SCK
D12/MISO
500mA charge
D18/A4/SDA
L-SHIFT
D26/A7
DEL

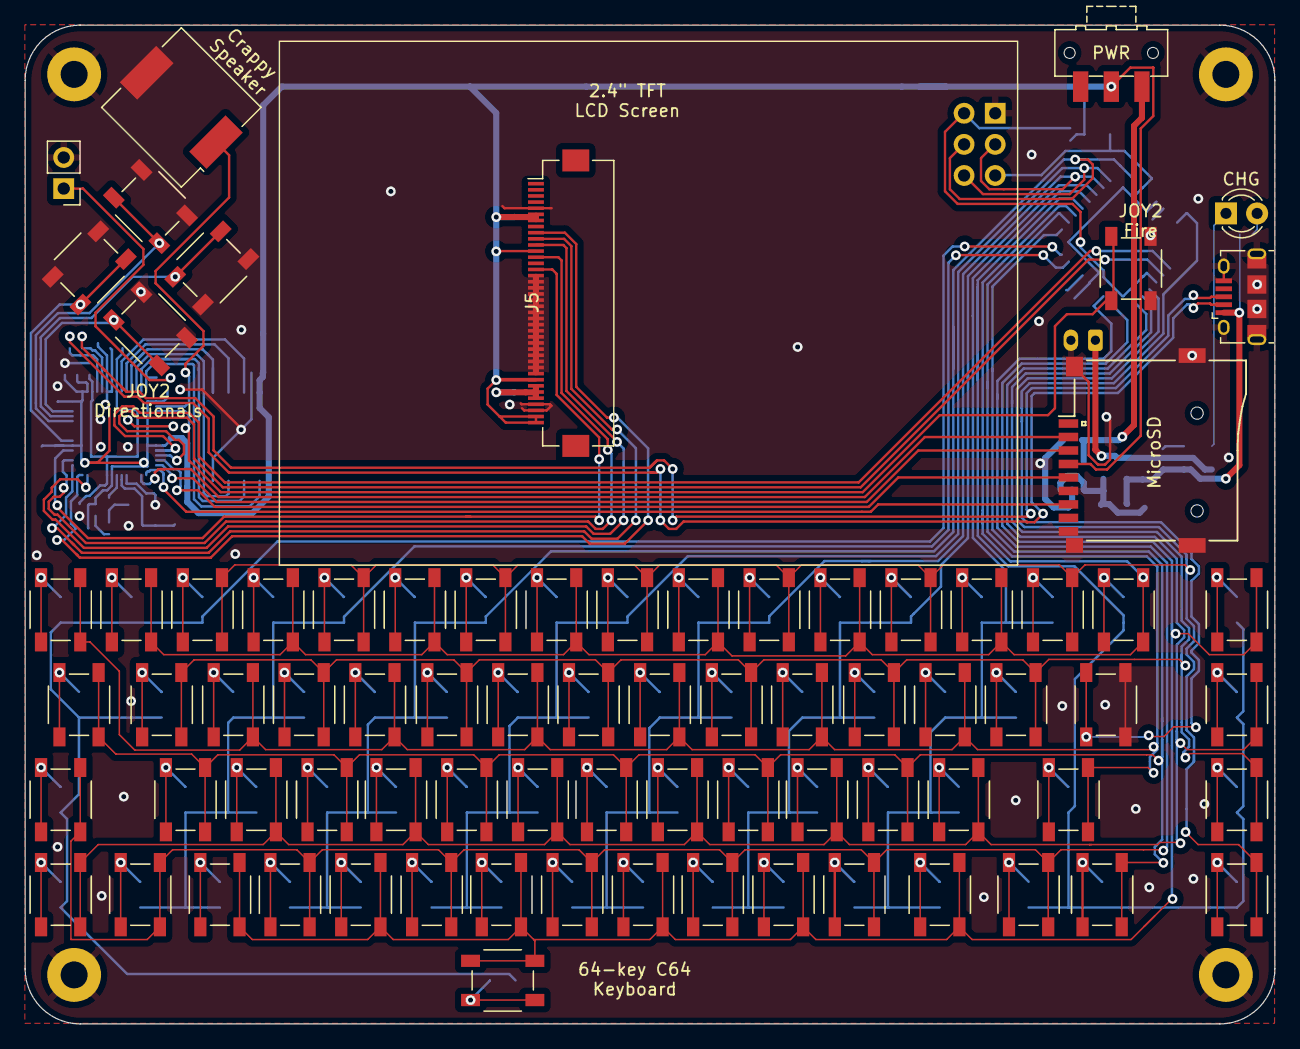
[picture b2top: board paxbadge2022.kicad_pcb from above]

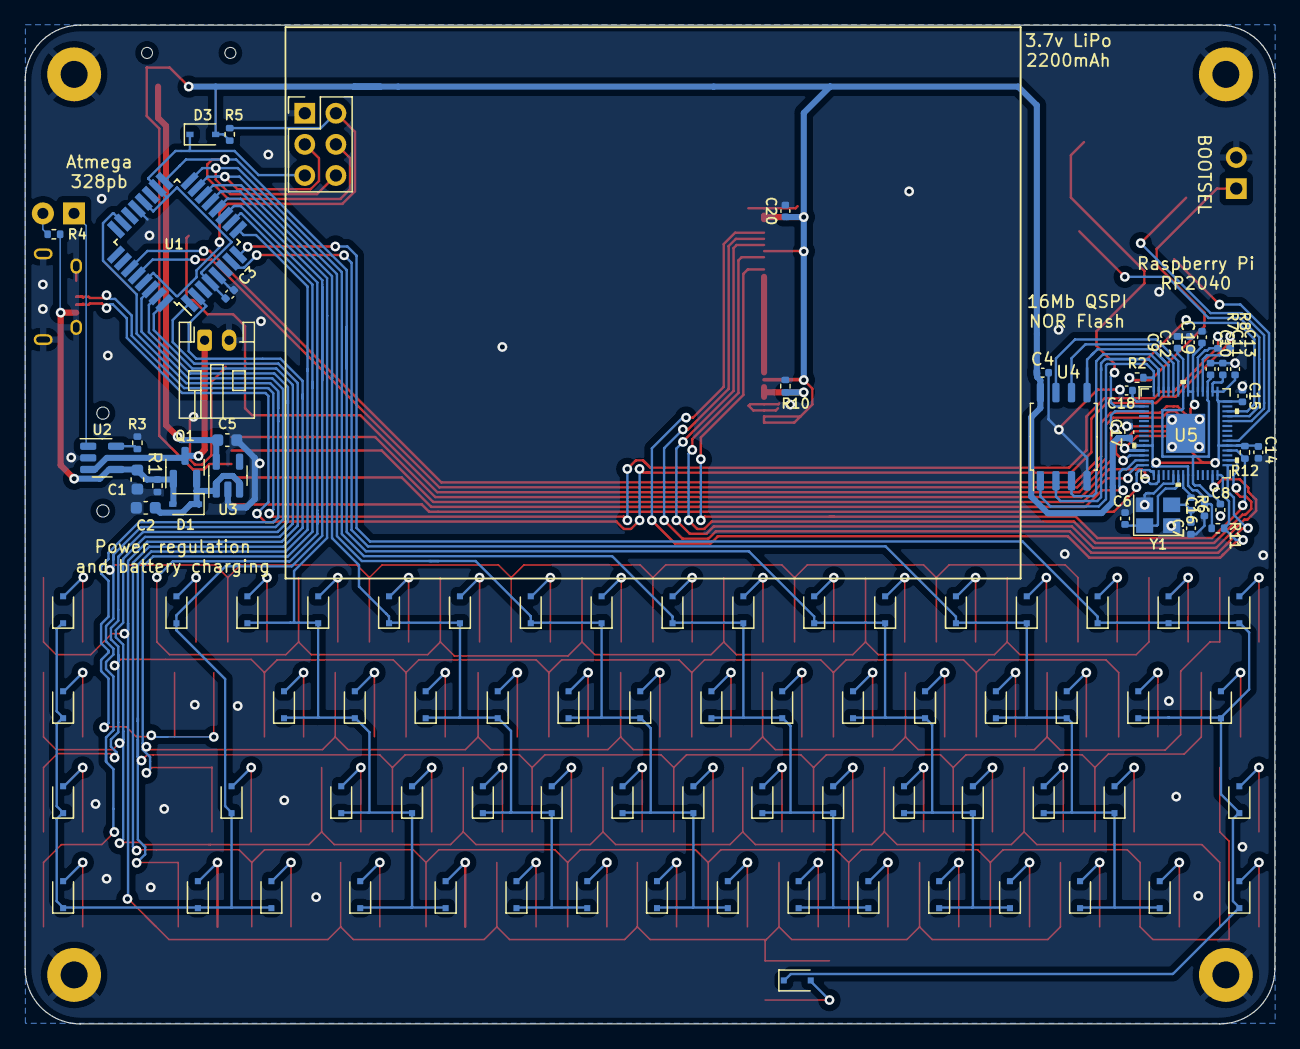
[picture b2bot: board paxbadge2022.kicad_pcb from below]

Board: 2 copper layers, 102.0 x 81.5 mm, 187 parts (106 on the bottom side), 125 nets.

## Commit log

2022-05-08 updated top cover
2022-05-09 nightly commit
2022-05-19 adding keyboard ino, syncing kicad after first prototype fixes
2022-10-15 clean up files for release
2022-10-15 adding license and readme, rename face/back plates
2022-10-15 update branch details
2022-11-08 add bom and update readme

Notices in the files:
parts and their libraries:
Copyright 2021 Accelerated Designs. All rights reserved.
